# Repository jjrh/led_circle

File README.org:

* about
  LED Circle encoder using the [[http://www.ti.com/lit/ds/symlink/tlc5940.pdf][TLC5940]]
  Idea is to have an encoder that will light up leds as it turns.

* make_placement.py
  Code to place the LEDs in a nice circle.
  Use caution when running this *WILL* overwrite the PCB.

* notes

  - kicad libraries are the super awesome http://smisioto.no-ip.org/elettronica/kicad/kicad-en.htm

** setup
   - You will need to put all the 3d libraries in the same place and set the $KISYS3DMOD variable.

    #+BEGIN_SRC sh
    cd ~/CODE/kicad/MyLib/smisioto/kicad_libs/modules/packages3d
    ln -s /usr/share/kicad/modules/packages3d/* .
    #+END_SRC

   - Keep in mind also that one will need to edit the led_circle.pro and fix the libraries.

* schematic
  - reference: https://www.pjrc.com/teensy/td_libs_Tlc5940.html

  #+CAPTION: schematic
  #+NAME:   fig:1
  #+attr_html: :width 800px
  [[./images/schematic/led_circle.sch.png]]

* PCB renders
** bare
  #+CAPTION: Bottom cu
  #+NAME:   fig:1
  #+attr_html: :width 800px
  [[./images/pcb/led_circle-B_Cu.png]]

  #+CAPTION: Front Coper
  #+NAME:   fig:2
  #+attr_html: :width 800px
  [[./images/pcb/led_circle-F_Cu.png]]

  #+CAPTION: Bottom Silk
  #+NAME:   fig:3
  #+attr_html: :width 800px
  [[./images/pcb/led_circle-B_SilkS.png]]

  #+CAPTION: Front Silk
  #+NAME:   fig:4
  #+attr_html: :width 800px
  [[./images/pcb/led_circle-F_SilkS.png]]

  #+CAPTION: board
  #+NAME:   fig:5
  #+attr_html: :width 800px
  [[./images/pcb/led_circle-brd.png]]

** 3D
  #+CAPTION: Top angled
  #+NAME:   fig:1
  #+attr_html: :width 800px
  [[./images/3d/led_circle_3d_1.png]]

  #+CAPTION: Bottom angled
  #+NAME:   fig:2
  #+attr_html: :width 800px
  [[./images/3d/led_circle_3d_2.png]]

  #+CAPTION: Top
  #+NAME:   fig:3
  #+attr_html: :width 800px
  [[./images/3d/led_circle_3d_top.png]]

  #+CAPTION: Bottom
  #+NAME:   fig:4
  #+attr_html: :width 800px
  [[./images/3d/led_circle_3d_bottom.png]]

  #+CAPTION: left
  #+NAME:   fig:5
  #+attr_html: :width 800px
  [[./images/3d/led_circle_3d_left.png]]

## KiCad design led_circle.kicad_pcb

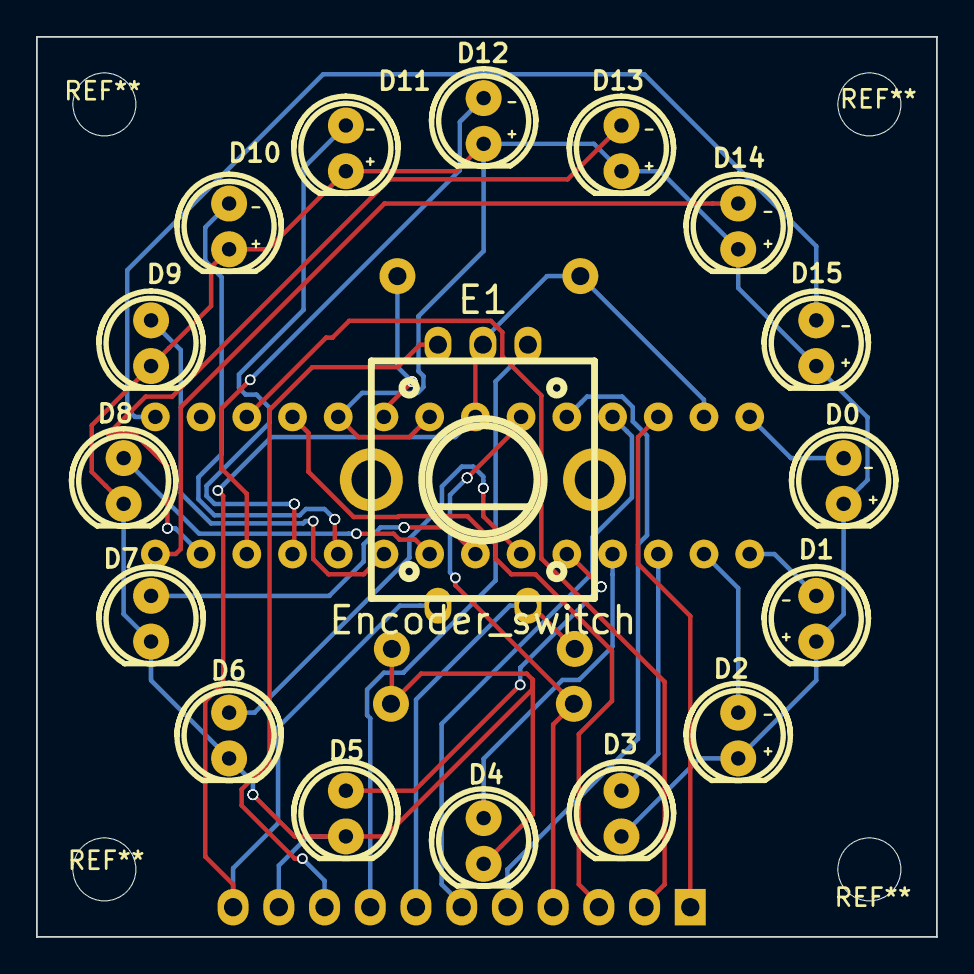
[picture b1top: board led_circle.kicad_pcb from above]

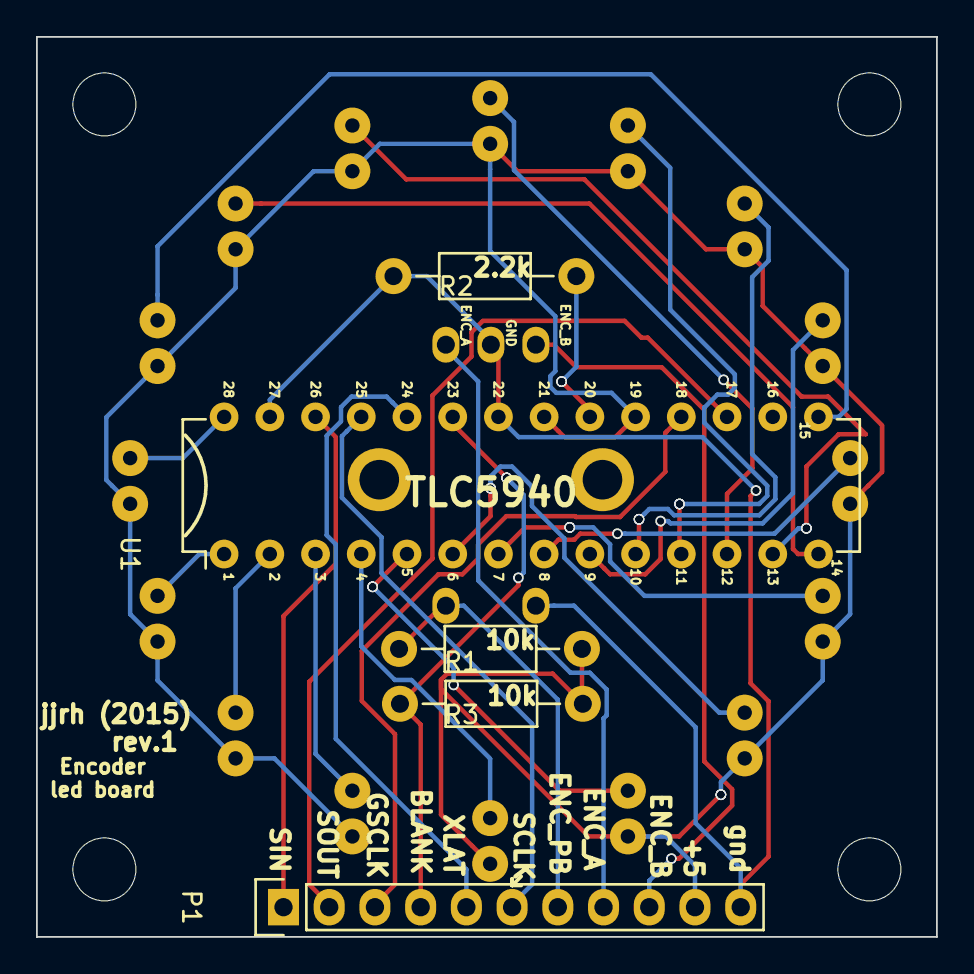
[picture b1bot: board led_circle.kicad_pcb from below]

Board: 2 copper layers, 50.0 x 50.0 mm, 22 parts (5 on the bottom side), 28 nets.

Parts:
D0, D1, D2, D3, D4, D5, D6, D7, D8, D9, D10, D11, D12, D13, D14, D15: LED; led_5mm_red
E1: Encoder_switch; encoder_alps-ec12d
P1: CONN_11; Pin_Header_Straight_1x11
R1, R3: 10k; Resistor_Horizontal_RM10mm
R2: 2.2k; Resistor_Horizontal_RM10mm
U1: TLC5940; DIP-28_W7.62mm

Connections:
+5V: D0.2, D1.2, D2.2, D3.2, D4.2, D5.2, D6.2, D7.2, D8.2, D9.2, D10.2, D11.2, D12.2, D13.2, D14.2, D15.2, P1.10, R1.2, R3.1, U1.19, U1.21
/BLANK: P1.4, R1.1, U1.23
/ENC_A: E1.1, P1.8
/ENC_B: E1.3, P1.9
/ENC_PB: E1.5, P1.7, R3.2
/GSCLK: P1.3, U1.18
/SCLK: P1.6, U1.25
/SIN: P1.1, U1.26
/SOUT: P1.2, U1.17
/XLAT: P1.5, U1.24
GND: E1.2, E1.4, P1.11, R2.1, U1.22, U1.27
unnamed: D0.1, U1.28
unnamed: D1.1, U1.1
unnamed: D2.1, U1.2
unnamed: D3.1, U1.3
unnamed: D4.1, U1.4
unnamed: D5.1, U1.5
unnamed: D6.1, U1.6
unnamed: D7.1, U1.7
unnamed: D8.1, U1.8
unnamed: D9.1, U1.9
unnamed: D10.1, U1.10
unnamed: D11.1, U1.11
unnamed: D12.1, U1.12
unnamed: D13.1, U1.13
unnamed: D14.1, U1.14
unnamed: D15.1, U1.15
unnamed: R2.2, U1.20

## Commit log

2015-06-14 initialized repo
2015-07-05 some various changes and missing stuff
2015-07-08 forgot to commit all the changes...
